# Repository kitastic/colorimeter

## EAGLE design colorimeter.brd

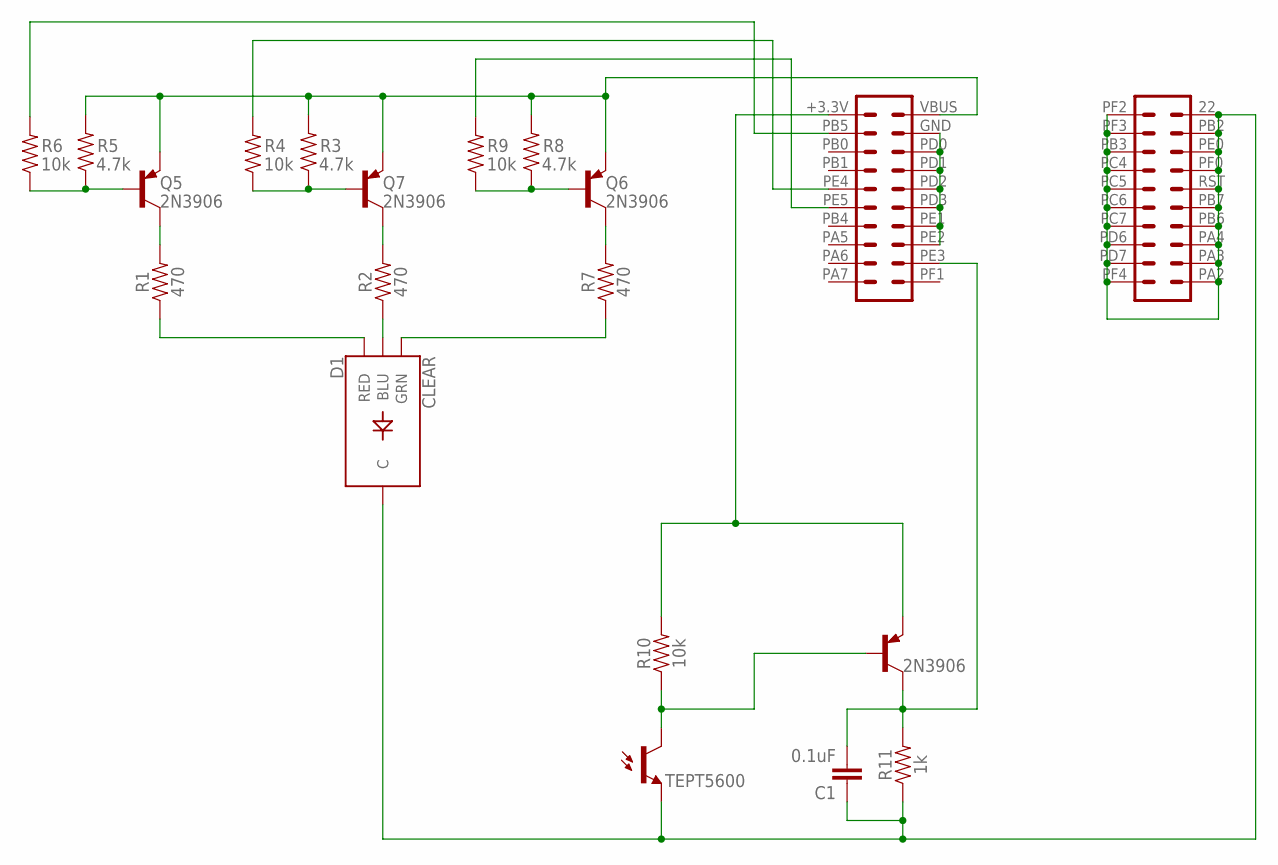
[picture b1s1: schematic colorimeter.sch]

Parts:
C1: 0.1uF; CAP-PTH-SMALL-KIT
D1: CLEAR; LED-RGB-THRU
Q1: TEPT5600; PT17-21C-L41-TR8
Q5, Q6, Q7: 2N3906; TO92-EBC-OVAL
R1, R2, R7: 470; AXIAL-0.3
R3, R5, R8: 4.7k; AXIAL-0.3
R4, R6, R9, R10: 10k; AXIAL-0.3
R11: 1k; AXIAL-0.3
T2: 2N3906; TO92-EBC
U$1: LAUNCHPAD_PINS

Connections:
unnamed: Q5.B, R5.P$1 (1), R6.P$1 (1)
unnamed: Q5.C, R1.P$2 (2)
unnamed: R9.P$2 (2), U$1.PE5 (31)
unnamed: R4.P$2 (2), U$1.PE4 (29)
unnamed: Q7.B, R3.P$1 (1), R4.P$1 (1)
unnamed: Q7.C, R2.P$2 (2)
unnamed: D1.1 (RED), R1.P$1 (1)
unnamed: R6.P$2 (2), U$1.PB5 (23)
unnamed: Q6.B, R8.P$1 (1), R9.P$1 (1)
unnamed: Q6.C, R7.P$2 (2)
unnamed: D1.4 (BLU), R2.P$1 (1)
unnamed: Q1.C, R10.P$1 (1), T2.B
unnamed: D1.3 (GRN), R7.P$1 (1)
unnamed: C1.2, R11.P$2 (2), T2.C, U$1.PE3 (38)
unnamed: R10.P$2 (2), T2.E, U$1.+3.3V (21)
unnamed: Q5.E, Q6.E, Q7.E, R3.P$2 (2), R5.P$2 (2), R8.P$2 (2), U$1.VBUS (22)
unnamed: C1.1, D1.2 (C), Q1.E, R11.P$1 (1), U$1.22 (2), U$1.PA2 (20), U$1.PA3 (18), U$1.PA4 (16), U$1.PB2 (4), U$1.PB3 (5), U$1.PB6 (14), U$1.PB7 (12), U$1.PC4 (7), U$1.PC5 (9), U$1.PC6 (11), U$1.PC7 (13), U$1.PD6 (15), U$1.PD7 (17), U$1.PE0 (6), U$1.PF0 (8), U$1.PF2 (1), U$1.PF3 (3), U$1.PF4 (19), U$1.RST (10)
unnamed: U$1.GND (24), U$1.PD0 (26), U$1.PD1 (28), U$1.PD2 (30), U$1.PD3 (32), U$1.PE1 (34), U$1.PE2 (36)

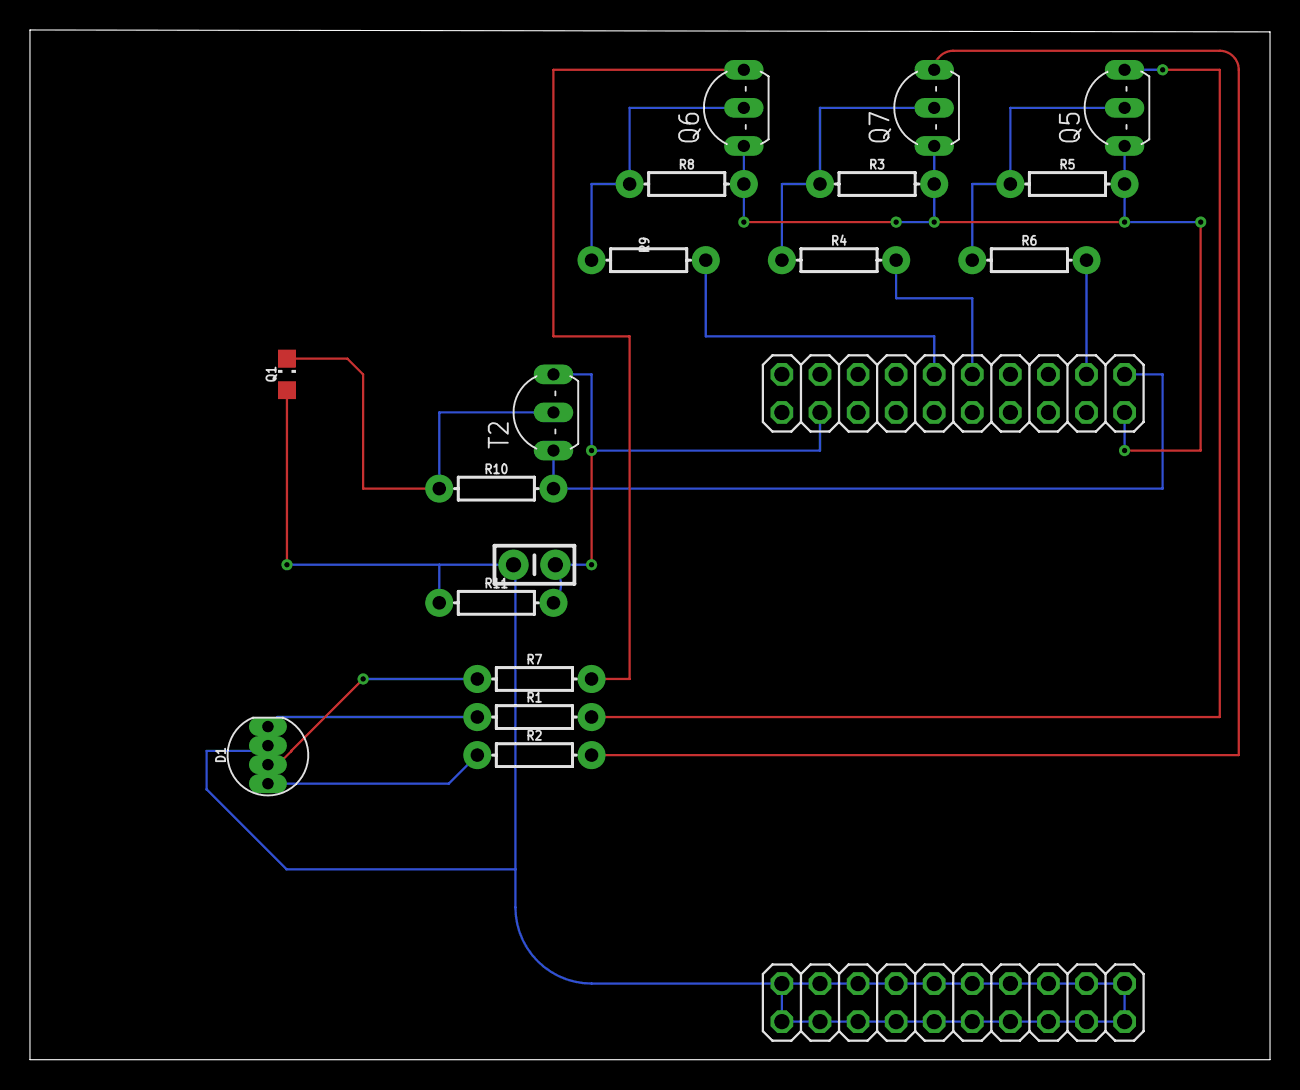
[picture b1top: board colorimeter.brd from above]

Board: 2 copper layers, 82.7 x 68.7 mm, 19 parts (0 on the bottom side), 18 nets.

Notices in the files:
parts and their libraries:
SparkFun-LED: Licensing: Creative Commons ShareAlike 4.0 International - https://creativecommons.org/licenses/by-sa/4.0
